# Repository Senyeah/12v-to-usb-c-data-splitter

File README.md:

# 12 V to USB-C data splitter

A car board that turns 12 V into 5 V at 3 A (15 W) on a USB-C socket for the phone, and passes the factory stereo's USB
data through to the same phone. I made it for a car stereo that talks to the phone over the old iPod USB protocol, and
an iPhone 15 Pro. The board does not use USB PD, so the iPhone keeps its USB data link to the stereo while it charges.

v1 is built, and it works great.

## Board

- Converter and USB switch: MPS MPQ4228-C (AEC-Q100), 420 kHz, line-drop compensation, BC1.2 CDP and Type-C Rp.
- Input: 2-pin 5.08 mm screw terminal, SMBJ33CA TVS, SS510 (100 V) reverse diode, LC filter.
- Stereo side: USB-B socket (J2). Phone side: USB-C socket (J3), to a panel-mount extension in the dash.
- LEDs: white is 5 V on, red is fault.
- 4 layers, 52 × 40 mm, 1.6 mm thick, two M3 holes.

## Files

- `fab/`: the Gerber zip to upload, the same files unzipped in `fab/gerber/`, JLCPCB BOM and CPL files in
  `fab/assembly/`, and schematic, assembly and layer PDFs in `fab/docs/`.
- `docs/`: 3D renders, an A5 schematic PDF and the photos above.
- The KiCad 10 project in the repo root, with the custom MPQ4228 symbol and footprint in `lib/`.
- `scripts/`: the KiCad Python scripts that built the schematic fields, the routing and the fab pack.
- `sim/`: ngspice simulation of the input chain and hand calculations, with results.

## Order at JLCPCB

JLCPCB was the cheapest fab I found. Upload the Gerber zip from `fab/`.

- PCB: 4 layers, 1.6 mm, qty 5, green. Keep JLC's defaults, including **Min via hole size 0.3mm/(0.4/0.45mm)**
  (all vias are 0.3 mm drill). The 0.25 mm option adds about US$37 (via fee plus a forced 4-wire Kelvin test).
- Assembly: Economic PCBA, top side, assemble 2 of the 5 boards.
- BOM: `fab/assembly/*-bom-jlc.csv`. CPL: `fab/assembly/*-cpl-jlc.csv`. In the BOM step, tick the "L3,L4,R9" (0R)
  line: JLC leaves it unselected.
- Tick Confirm Parts Placement (US$0.45). JLC engineers then check the rotations of U1, D1–D6, C1 and J3. JLC's preview
  shows J3 offset towards the board edge.
- Product description (customs): "DIY Hobby Circuit Board – HS Code 902300".
- Shipping: Global Standard Direct Line (US$7.24 to NZ, 10–15 business days, orders up to US$150).

JLCPCB quote on 07/10/2026 for 5 boards with 2 assembled:

| Line | US$ |
|---|---|
| PCB | 8.00 (2.00 through the JLCONE desktop app) |
| Setup 8.24 + stencil 1.55 | 9.79 |
| Components, 30 lines | 14.27 |
| Extended components fee (U1, J3, C1, L1, L2, C2/C3, D3/D4) | 21.63 |
| SMT assembly, placement check, nitrogen reflow | 1.88 |
| Shipping, Global Standard Direct Line | 7.24 |
| Automatic cart coupon | −10.00 |
| **Total before GST** | **≈ 52.81 (≈ NZ$90)**; ≈ US$61 / NZ$103 with 15 % GST |

The GST line and new-user coupons only show at checkout, after you enter the shipping address.

J1 (screw terminal) and J2 (USB-B) are through-hole. If you do not want to solder anything, upload
`fab/assembly/*-with-tht-bom-jlc.csv` and `fab/assembly/*-with-tht-cpl-jlc.csv` instead. JLC then hand-solders both
parts in Economic PCBA for US$5.61 more (US$61.18 instead of US$55.57 on 07/10/2026; hand-soldered parts have no
extended fee). Otherwise buy C7509570 and C19944605 and solder the 10 joints yourself.

The CPL files shift J1, J2 and J3 so that JLC's (EasyEDA) footprint origins land on the KiCad footprints (`CPL_FIX` in
`scripts/jlc_files.py`). Without the shift, JLC's preview puts J3 1.42 mm towards the board edge.

On 07/10/2026 PCBWay, Seeed, ALLPCB, NextPCB and Elecrow were all more expensive for 2 assembled boards. NextPCB's
"Rev 0" free assembly offer could be cheaper, but it needs a live quote and its parts do not come from LCSC.

## Parts for the car

| Item | Source | NZ$ |
|---|---|---|
| Panel-mount USB-C male-to-female extension, USB 3.1 type (passes CC) | [AliExpress 1005010641105986](https://www.aliexpress.com/item/1005010641105986.html) | ≈ 6.30 |
| Short USB-A male to USB-B male cable | [AliExpress 32700175631](https://www.aliexpress.com/item/32700175631.html) or a spare printer cable | 0–5.60 |
| Micro2 add-a-circuit fuse tap and a 5 A Micro2 fuse | [AliExpress 1005006019784140](https://www.aliexpress.com/item/1005006019784140.html) or a car parts shop | ≈ 0.50–8 |
| 0.75–1 mm² wire, ring terminal for ground | on hand | |

Wiring: console USB-A socket → USB-A to USB-B cable → J2. J3 → panel-mount USB-C extension → phone. Fuse tap on an ACC
fuse → 5 A fuse → J1 "+12V". J1 "GND" → body ground near the stereo. The stereo's 5 V does not connect to anything on
the board.

## Bring-up

1. Before you apply power, measure J1 + to GND and J3 VBUS to GND. Neither may be a short.
2. Bench supply at 12 V with a 0.5 A limit, no phone. The white LED is on and the red LED is off. J3 VBUS reads about
   5.0 V only after a sink is attached (the phone, or a USB-C to USB-A adapter with a load). Idle input current is
   about 15–25 mA, because the chip switches all the time (forced CCM at 420 kHz) and the white LED is on.
3. Phone on the bench, 12 V with a 2 A limit: the iPhone shows that it is charging, and the input draws about 1.4 A at
   12 V for 15 W.
4. In the car, the stereo sees the iPod as before and the phone charges.
5. Before you fit the panel extension, measure its female A5 to B5 with a meter. It must be open (CC1 and CC2 not
   joined), and each pin must reach the plug. Joined CC lines look like a debug accessory, and U1 then keeps VBUS off.
6. At 12 V and a 3 A load, feel or measure D2 (SS510): it dissipates about 1 W. In the car (14 V) it is about 0.8 W.
7. Unplug the phone at full load and watch the red LED. A flash means that the USB_IN OVP (5.85 V min) tripped on the
   load release. If it does, lower the line-drop gain (R7 27k with R8 5.1k).

VBUS on J3 stays at 0 V until a sink attaches. That is correct: the white LED shows VOUT, not VBUS.

## Design notes

- Output set point is 0.792 V × (1 + 30k/5.6k) = 5.03 V. ADJ adds about 2 µA/A × 30 kΩ, so +0.18 V at 3 A to
  compensate for cable drop.
- L3/L4 (18 nH eye-diagram tuning in the MPS reference design) are fitted as 0 Ω, and C29 (3.3 pF) is not fitted, so
  that every passive is a JLC basic part. If USB data is unreliable, fit 18 nH (C6807995) and 3.3 pF.
- The MPQ4228 footprint in `lib/` is drawn from the datasheet land pattern. Compare it with the JLC footprint preview
  before you pay.
- The MPQ4228 is rated 40 V absolute maximum, and the SMBJ33CA starts to conduct at 36.7 V. The LC filter and C1 keep
  VIN1 at or below 34.4 V in every simulated ISO pulse (see Checks).
- The red FAULT LED loads VCC2 (the 3.45 V internal LDO) with about 1.5 mA, but only while FLT is low.
- The VOUT feed to U1 USB_IN runs on In2 (0.5 oz) and, in parallel, on a 1 oz B.Cu strip (x 116.6–118.4). The B.Cu
  path carries about two thirds of the 3 A. This avoids JLC's US$18 charge for 1 oz inner copper.

## Checks (07/10/2026)

MPS publishes no SPICE model for the MPQ4228 (SIMPLIS only), so the converter itself is not simulated.

- `sim/input_sim.py` (ngspice) models the input chain with the chip as a 17.7 W constant-power load, through ISO
  7637-2 and ISO 16750-2 pulses at both SMBJ33CA tolerance ends. Results are in `sim/results.md`. Everything passes
  except the unsuppressed 87 V load dump (about 230 J into the TVS), which no small TVS survives. The board relies on
  the car's alternator load-dump suppression, and a shorted TVS blows the 5 A fuse. Pulse 1 put 60.6 V across the
  first-choice SS56 (60 V), so D2 is now an SS510 (100 V, 75.9 V seen). The input filter is stable, with at least 9 dB
  margin at 6 V input.
- `sim/calcs.py`: output voltage 4.85–5.22 V at no load and at most 5.45 V at 3 A worst case; L1 peak at most 5.31 A
  (Isat 5.5 A); U1 Tj ≈ 100–122 °C and D2 Tj ≈ 118 °C at 60–70 °C ambient. Results are in `sim/calcs.md`.
- A separate AI design review found that the pin map, D+/D− routing, Type-C DFP and CDP set-up, footprint land pattern
  and passive values all match the datasheet. It added 10 GND vias (U1 heat path, C4 return, D3/D4 ESD return). An
  SMBJ24CA was rejected because it burns in a 35 V suppressed load dump in simulation. Open, low-risk items: FB/FREQ
  trace lengths, D3/D4 are polarised (the JLC placement check covers this), and there are no ESD diodes on the J2 side.
- Not covered: control-loop stability, load-step response and EMI.

## Scripts

Run the scripts with KiCad's Python (`/Applications/KiCad/KiCad.app/Contents/Frameworks/Python.framework/Versions/3.9/bin/python3`
on macOS). They assume KiCad 10 in `/Applications`.

- `scripts/make_lib.py` (symbol and footprint), then `add_fields.py` and `cost_parts.py` (JLC basic part swaps) on the
  schematic.
- `scripts/rename_nets.py`, then `sync_parity.py` (board from the schematic netlist).
- `scripts/copper.py <board> --routing`, then `route.py <board> <workdir>` (Freerouting, expected at
  `~/.kicad-mcp/freerouting.jar`), then `copper.py <board>`.
- `scripts/silk.py`, then `scripts/fab.sh` to write `fab/`.
- `uv run sim/input_sim.py` and `python3 sim/calcs.py` for the checks.

## Licence

CERN Open Hardware Licence Version 2, Strongly Reciprocal (CERN-OHL-S-2.0). See [LICENSE](LICENSE).
Source: https://github.com/Senyeah/12v-to-usb-c-data-splitter

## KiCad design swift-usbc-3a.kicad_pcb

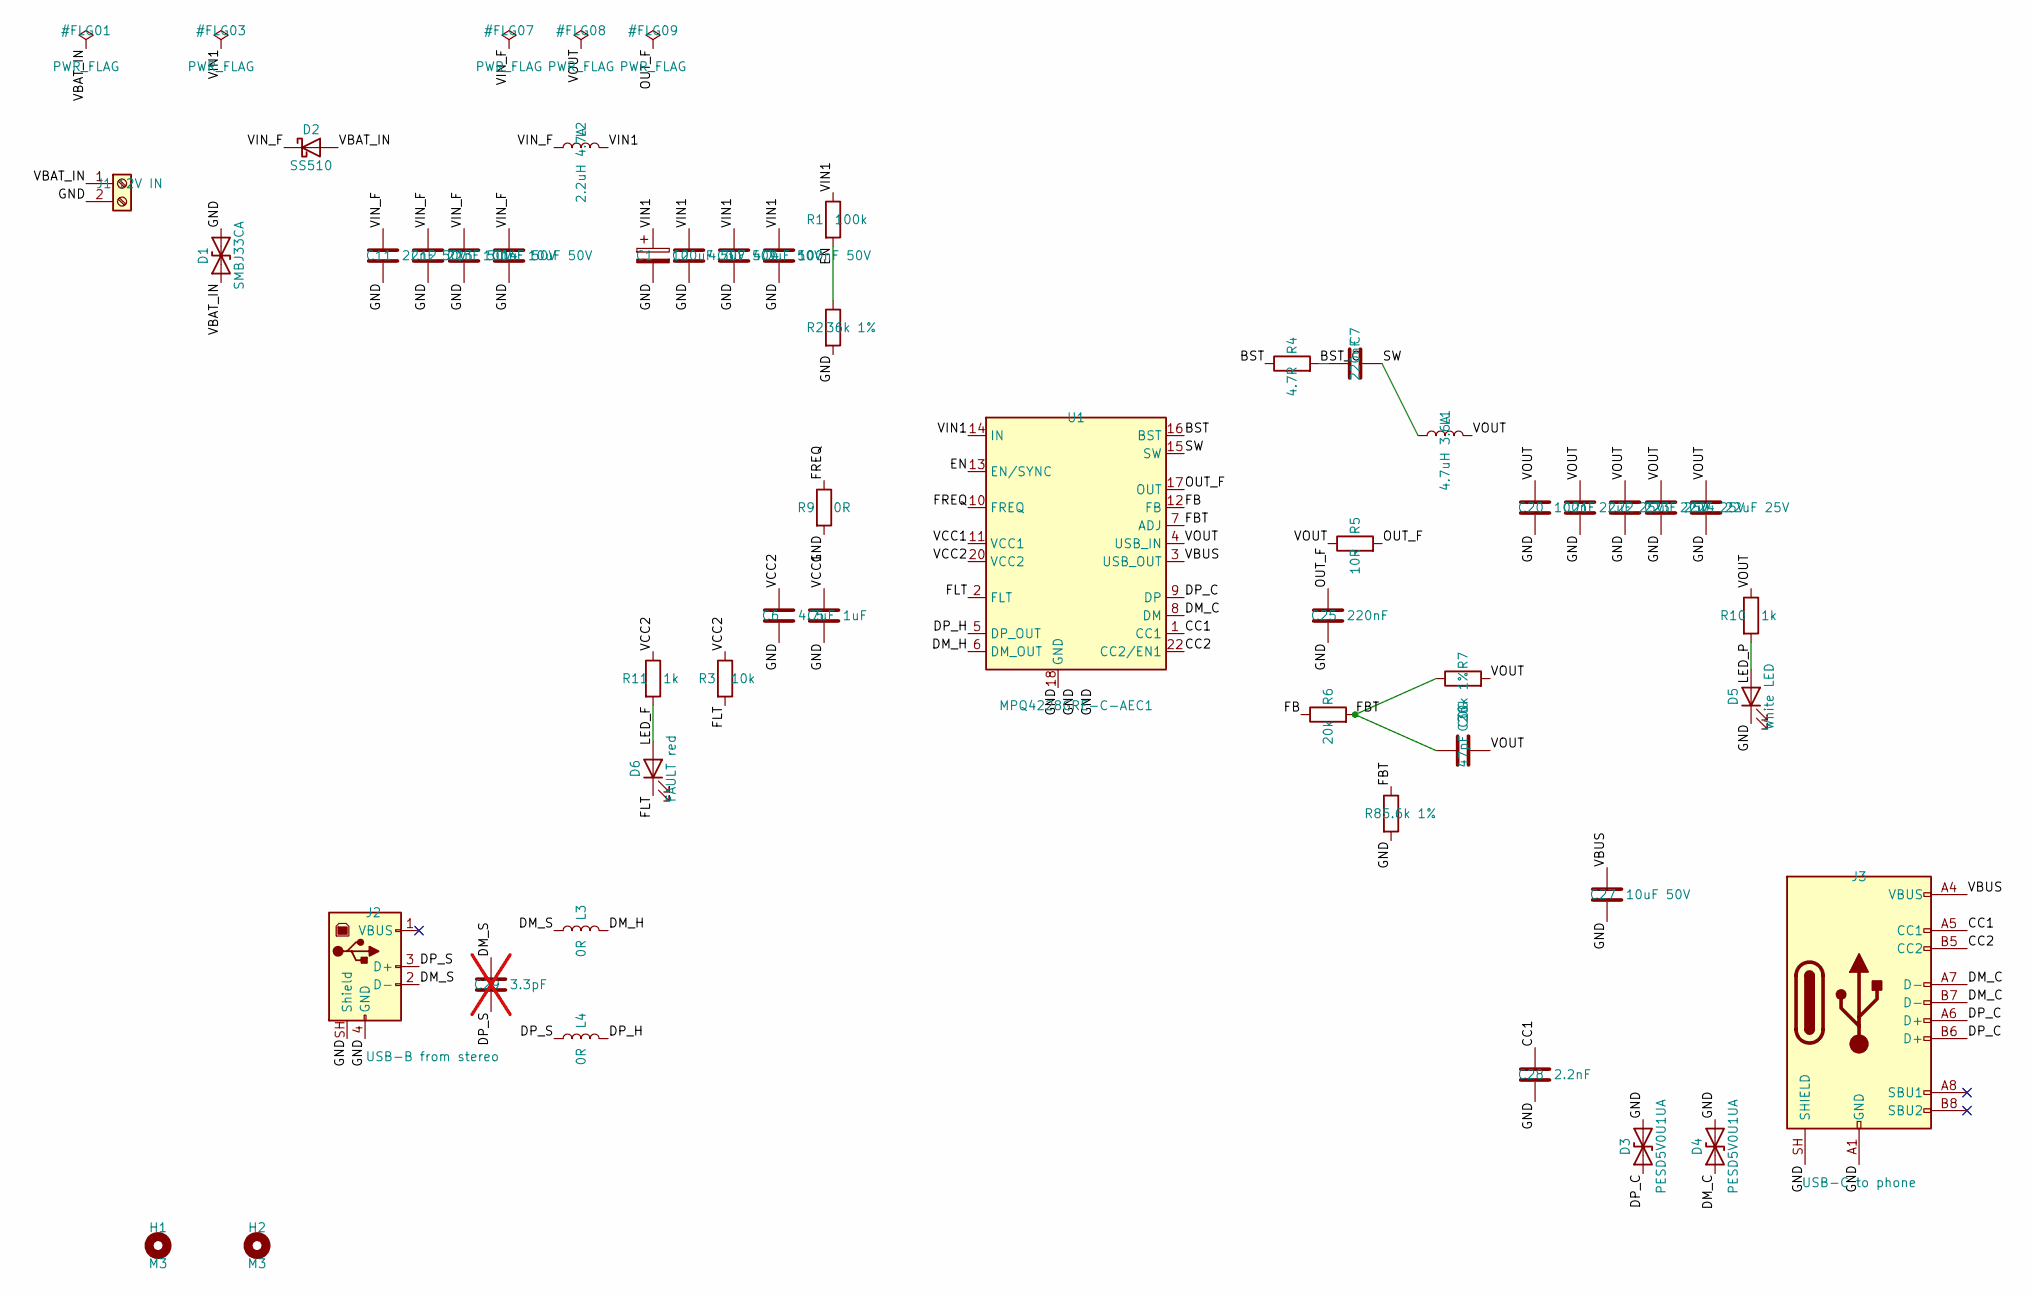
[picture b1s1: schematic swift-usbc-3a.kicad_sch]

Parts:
C1: 100uF 50V; CP_Elec_8x10.5; LCSC C19184158
C2, C3: 4.7uF 50V; C_0805_2012Metric; LCSC C20416422
C4, C13: 100nF 50V; C_0603_1608Metric; LCSC C14663
C5: 1uF; C_0603_1608Metric; LCSC C15849
C6: 4.7uF; C_0603_1608Metric; LCSC C19666
C7, C25: 220nF; C_0603_1608Metric; LCSC C21120
C11, C12: 22nF 50V; C_0603_1608Metric; LCSC C21122
C14, C27: 10uF 50V; C_1206_3216Metric; LCSC C13585
C20: 100nF; C_0603_1608Metric; LCSC C14663
C21, C22, C23, C24: 22uF 25V; C_1206_3216Metric; LCSC C12891
C26: 47pF C0G; C_0603_1608Metric; LCSC C1671
C28: 2.2nF; C_0603_1608Metric; LCSC C1604
C29: 3.3pF; C_0603_1608Metric; LCSC C7227538; not fitted
D1: SMBJ33CA; D_SMB; LCSC C19077587
D2: SS510; D_SMA; LCSC C18199171
D3, D4: PESD5V0U1UA; D_SOD-323; LCSC C19829579
D5: White LED; LED_0603_1608Metric; LCSC C2290
D6: FAULT red; LED_0603_1608Metric; LCSC C2286
H1, H2: M3; MountingHole_3.2mm_M3
J1: 12V IN; TerminalBlock_Phoenix_MKDS-1,5-2-5.08_1x02_P5.08mm_Horizont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; LCSC C7509570
J2: USB-B from stereo; USB_B_OST_USB-B1HSxx_Horizontal; LCSC C19944605
J3: USB-C to phone; USB_C_Receptacle_HRO_TYPE-C-31-M-12; LCSC C165948
L1: 4.7uH 3.6A; L_APV_ANR6045; LCSC C6808109
L2: 2.2uH 4.7A; L_Changjiang_FTC303020D; LCSC C7423318
L3, L4: 0R; L_0603_1608Metric; LCSC C21189
R1: 100k; R_0603_1608Metric; LCSC C25803
R2: 36k 1%; R_0603_1608Metric; LCSC C23147
R3: 10k; R_0603_1608Metric; LCSC C25804
R4: 4.7R; R_0603_1608Metric; MPN 0603WAF470KT5E; LCSC C23164
R5: 10R; R_0603_1608Metric; LCSC C22859
R6: 20k; R_0603_1608Metric; LCSC C4184
R7: 30k 1%; R_0603_1608Metric; LCSC C22984
R8: 5.6k 1%; R_0603_1608Metric; LCSC C23189
R9: 0R; R_0603_1608Metric; LCSC C21189
R10, R11: 1k; R_0603_1608Metric; LCSC C21190
U1: MPQ4228GRE-C-AEC1; MPS_QFN-22_4x4mm_P0.5mm; MPN MPQ4228GRE-C-AEC1-Z; LCSC C17638787

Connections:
/BST: R4.1, U1.16 (BST)
/BST_C: C7.1, R4.2
/CC1: C28.1, J3.A5 (CC1), U1.1 (CC1)
/CC2: J3.B5 (CC2), U1.22 (CC2/EN1)
/DM_C: D4.1 (A1), J3.A7 (D-), J3.B7 (D-), U1.8 (DM)
/DM_H: L3.2, U1.6 (DM_OUT)
/DM_S: C29.1, J2.2 (D-), L3.1
/DP_C: D3.1 (A1), J3.A6 (D+), J3.B6 (D+), U1.9 (DP)
/DP_H: L4.2, U1.5 (DP_OUT)
/DP_S: C29.2, J2.3 (D+), L4.1
/EN: R1.2, R2.1, U1.13 (EN/SYNC)
/FB: R6.1, U1.12 (FB)
/FBT: C26.1, R6.2, R7.1, R8.1, U1.7 (ADJ)
/FLT: D6.1 (K), R3.2, U1.2 (FLT)
/FREQ: R9.1, U1.10 (FREQ)
/GND: C1.2, C2.2, C3.2, C4.2, C5.2, C6.2, C11.2, C12.2, C13.2, C14.2, C20.2, C21.2, C22.2, C23.2, C24.2, C25.2, C27.2, C28.2, D1.2 (A2), D3.2 (A2), D4.2 (A2), D5.1 (K), J1.2, J2.4 (GND), J2.SH (Shield), J3.A1 (GND), J3.A12 (GND), J3.B1 (GND), J3.B12 (GND), J3.SH (SHIELD), R2.2, R8.2, R9.2, U1.18 (GND), U1.19 (GND), U1.21 (GND)
/LED_F: D6.2 (A), R11.2
/LED_P: D5.2 (A), R10.2
/OUT_F: C25.1, R5.2, U1.17 (OUT)
/SW: C7.2, L1.1, U1.15 (SW)
/VBAT_IN: D1.1 (A1), D2.2 (A), J1.1
/VBUS: C27.1, J3.A4 (VBUS), J3.A9 (VBUS), J3.B4 (VBUS), J3.B9 (VBUS), U1.3 (USB_OUT)
/VCC1: C5.1, U1.11 (VCC1)
/VCC2: C6.1, R3.1, R11.1, U1.20 (VCC2)
/VIN1: C1.1, C2.1, C3.1, C4.1, L2.2, R1.1, U1.14 (IN)
/VIN_F: C11.1, C12.1, C13.1, C14.1, D2.1 (K), L2.1
/VOUT: C20.1, C21.1, C22.1, C23.1, C24.1, C26.2, L1.2, R5.1, R7.2, R10.1, U1.4 (USB_IN)

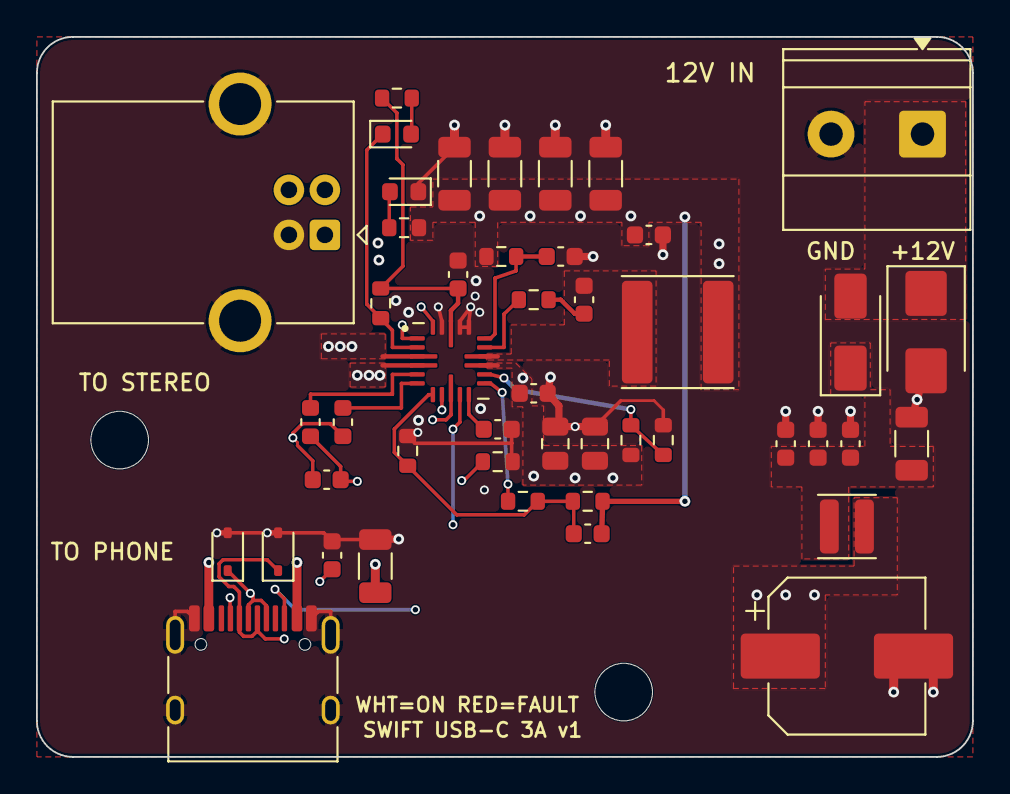
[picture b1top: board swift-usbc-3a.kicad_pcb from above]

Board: 4 copper layers, 52.0 x 40.0 mm, 48 parts (0 on the bottom side), 27 nets.

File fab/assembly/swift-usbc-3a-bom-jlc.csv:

Comment,Designator,Footprint,LCSC Part #
100uF 50V,C1,CP_Elec_8x10.5,C19184158
4.7uF 50V,"C2,C3",C_0805_2012Metric,C20416422
100nF 50V,"C4,C13,C20",C_0603_1608Metric,C14663
1uF,C5,C_0603_1608Metric,C15849
4.7uF,C6,C_0603_1608Metric,C19666
220nF,"C7,C25",C_0603_1608Metric,C21120
22nF 50V,"C11,C12",C_0603_1608Metric,C21122
10uF 50V,"C14,C27",C_1206_3216Metric,C13585
22uF 25V,"C21,C22,C23,C24",C_1206_3216Metric,C12891
47pF C0G,C26,C_0603_1608Metric,C1671
2.2nF,C28,C_0603_1608Metric,C1604
SMBJ33CA,D1,D_SMB,C19077587
SS510,D2,D_SMA,C18199171
PESD5V0U1UA,"D3,D4",D_SOD-323,C19829579
White LED,D5,LED_0603_1608Metric,C2290
FAULT red,D6,LED_0603_1608Metric,C2286
USB-C to phone,J3,USB_C_Receptacle_HRO_TYPE-C-31-M-12,C165948
4.7uH 3.6A,L1,L_APV_ANR6045,C6808109
2.2uH 4.7A,L2,L_Changjiang_FTC303020D,C7423318
0R,"L3,L4,R9",L_0603_1608Metric,C21189
100k,R1,R_0603_1608Metric,C25803
36k 1%,R2,R_0603_1608Metric,C23147
10k,R3,R_0603_1608Metric,C25804
4.7R,R4,R_0603_1608Metric,C23164
10R,R5,R_0603_1608Metric,C22859
20k,R6,R_0603_1608Metric,C4184
30k 1%,R7,R_0603_1608Metric,C22984
5.6k 1%,R8,R_0603_1608Metric,C23189
1k,"R10,R11",R_0603_1608Metric,C21190
MPQ4228GRE-C-AEC1,U1,MPS_QFN-22_4x4mm_P0.5mm,C17638787

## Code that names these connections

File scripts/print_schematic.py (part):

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    # ---- U1 support parts (left) -----------------------------------------------------------------
    cy = 20.4
    text(d, (14.5, 21.15), "U1 support", 4.4, color="#777777")
    netlabel(d, (10.0, cy), "FREQ", C_CTL, "left")
    wire(d, [(10.0, cy), (11.0, cy)], C_CTL)
    vpart(d, elm.Resistor, (11.0, cy), 1.4, ["R9 0R", "420 kHz"])
    netlabel(d, (14.0, cy), "VCC1", C_CTL, "left")
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    wire(d, [(21.6, cy - 1.6), (21.6, 17.0), (24.0, 17.0), (24.0, cy - 2.4)], C_CTL)
    dot(d, (21.6, 17.0), C_CTL)
    wire(d, [(21.6, 17.0), (20.6, 17.0)], C_CTL)
    netlabel(d, (20.6, 17.0), "FLT", C_CTL, "left")
    text(d, (22.8, 16.5), "red LED on = fault", 3.9, color="#666666")

    # ---- Output: bootstrap, L1, caps, power LED --------------------------------------------------
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    d += elm.LED().at((52.4, 21.8)).down(1.2).color(C_GND).linewidth(0.8)
    text(d, (53.15, 21.2), "D5 white", FS, halign="left", color=C_5V)
    gnd(d, (52.4, 20.6))
    netlabel(d, (54.0, 23.0), "VOUT", C_5V)

    # ---- Feedback and OUT sense (right) ----------------------------------------------------------
    fy = 18.8
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    dot(d, (41.4, fy), C_CTL)
    d += elm.Resistor().at((42.2, fy)).right(1.6).color(C_GND).linewidth(0.8).label("R7 30k 1%", loc="bottom", fontsize=FS, ofst=0.08)
    wire(d, [(43.8, fy), (44.6, fy)], C_CTL)
    netlabel(d, (44.6, fy), "VOUT", C_5V)
    wire(d, [(41.4, fy), (41.4, fy + 0.9), (42.5, fy + 0.9)], C_CTL)
    d += elm.Capacitor().at((42.5, fy + 0.9)).right(0.7).color(C_GND).linewidth(0.8)
    wire(d, [(43.2, fy + 0.9), (44.2, fy + 0.9), (44.2, fy)], C_CTL)
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    wire(d, [(41.4, fy), (41.4, fy - 0.6)], C_CTL)
    vpart(d, elm.Resistor, (41.4, fy - 0.6), 1.4, ["R8", "5.6k 1%"])
    text(d, (40.85, fy - 1.25), "FBT\n(ADJ)", FSN, C_CTL, halign="right")
    netlabel(d, (48.8, fy), "VOUT", C_5V, "left")
    wire(d, [(48.8, fy), (49.0, fy)], C_5V)
    hpart(d, elm.Resistor, (49.0, fy), 1.4, "R5", "10R")
    wire(d, [(50.4, fy), (51.4, fy)], C_CTL)
    dot(d, (51.0, fy), C_CTL)
    vpart(d, elm.Capacitor, (51.0, fy), 1.3, ["C25", "220n"])
    netlabel(d, (51.4, fy), "OUT_F", C_CTL)

    # ---- USB-C side: fan-out to J3 ---------------------------------------------------------------
    jx, jy0, jy1 = 49.0, 3.4, 16.5
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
